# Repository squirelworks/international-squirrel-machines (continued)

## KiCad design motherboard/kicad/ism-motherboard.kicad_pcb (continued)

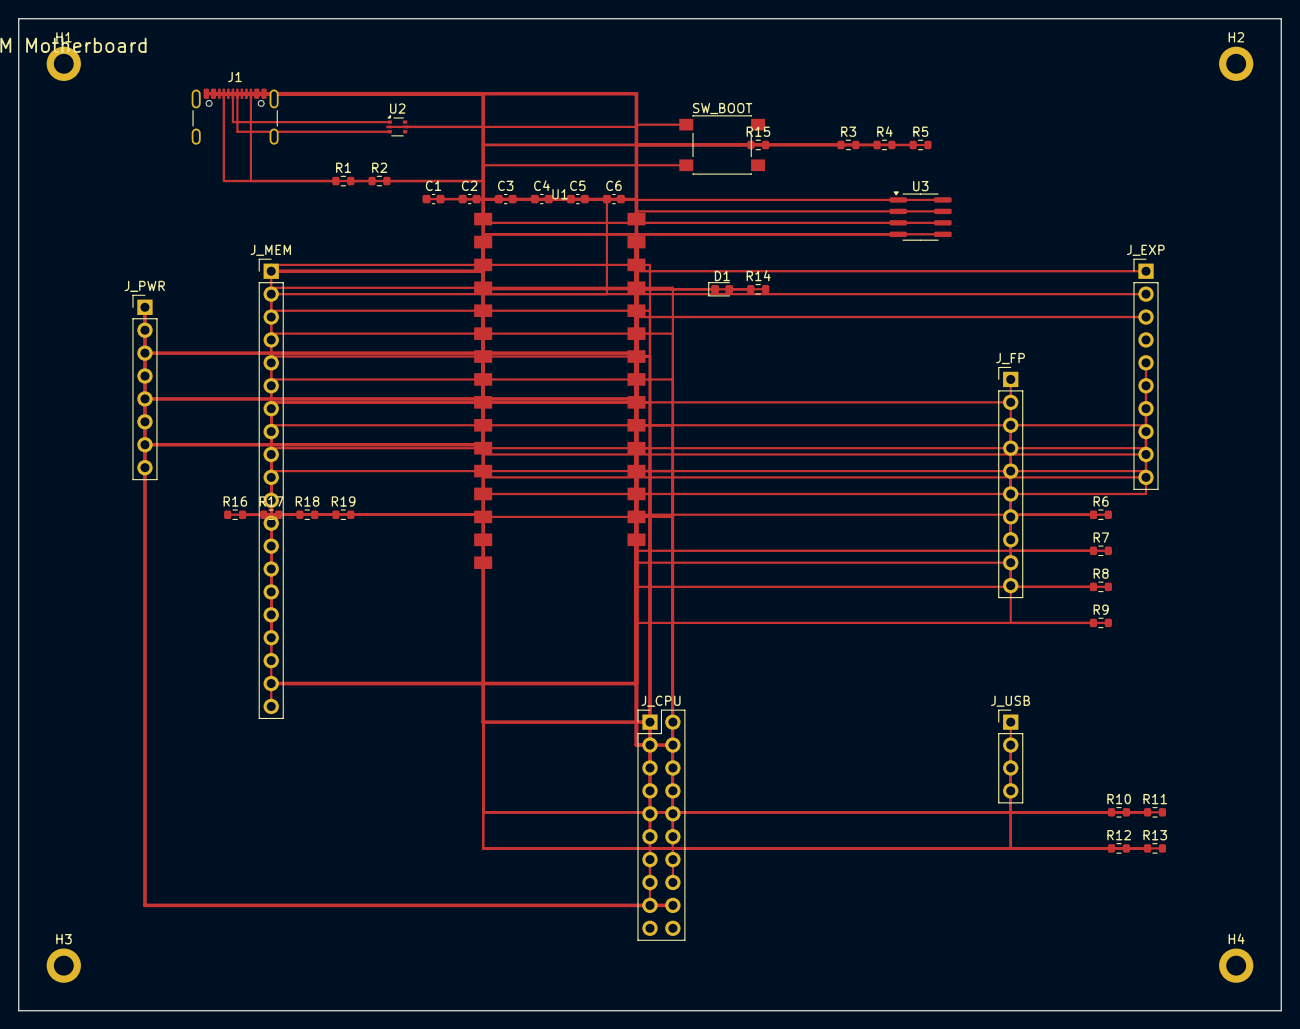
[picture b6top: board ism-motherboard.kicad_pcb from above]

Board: 4 copper layers, 140.0 x 110.0 mm, 41 parts (0 on the bottom side), 42 nets.

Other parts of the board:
H1, H2, H3, H4: M2; MountingHole_2.2mm_M2_DIN965_Pad

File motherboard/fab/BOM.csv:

Designator,Value,Footprint,Quantity,Manufacturer,MPN,LCSC,Notes
U1,RP2040_MOD,ISM_RP2040_Module,1,ISM,ISM-RP2040-MOD,,No LCSC — BMC / southbridge stand-in
U2,USBLC6-2SC6,SOT-666,1,ST,USBLC6-2SC6,C7519,ESD
U3,24LC02,SOIC-8,1,Microchip,24LC02B,C7500,Board ID
J1,USB4105,GCT USB-C 16P,1,GCT,USB4105-GF-A,C165948,BMC USB
J_PWR,ATX_PWR,PinHeader 1x08,1,,HDR-1x8,C124412,Bring-up power
J_MEM,MEM20,PinHeader 1x20,1,,HDR-1x20,C124419,Memory net map
J_CPU,CPU20,PinHeader 2x10,1,,HDR-2x10,C124384,CPU module
J_FP,ATX_FP,PinHeader 1x10,1,,HDR-1x10,C124413,Case FP
J_USB,MB_USB,PinHeader 1x04,1,,HDR-1x4,C124423,Case USB
J_EXP,EXP10,PinHeader 1x10,1,,HDR-1x10,C124413,Expansion
"R1,R2",5.1k,0603,2,,5.1k,C23244,CC
"R3,R4",4.7k,0603,2,,4.7k,C23141,I2C
"R5,R8,R9,R10-R13,R15-R19",10k,0603,13,,10k,C25804,
"R6,R7,R14",1k,0603,3,,1k,C21190,
C1-C6,100nF,0603,6,,100nF,C14663,
D1,LED,0603,1,,LED,C2286,
SW_BOOT,PTS645,PTS645,1,,PTS645,C318884,
H1-H4,M2,MountingHole,4,,,,No LCSC — mechanical NPTH

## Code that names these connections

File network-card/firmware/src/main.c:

/*
 * ISM Network Card firmware — SPI master bring-up for W5500 + EXP slave pins.
 * Module pad N → GP(N-2) for pads 2..13 (ISM convention).
 */
#include "pico/stdlib.h"
#include "hardware/gpio.h"
#include "hardware/spi.h"
#include "tusb.h"

#define PIN_EXP_SCK   0
#define PIN_EXP_MOSI  1
#define PIN_EXP_MISO  2
#define PIN_EXP_CS    3
#define PIN_ETH_SCLK  4  /* pad 6 */
#define PIN_ETH_MOSI  5  /* pad 7 */
#define PIN_ETH_MISO  6  /* pad 8 */
#define PIN_ETH_CS    7  /* pad 9 */
#define PIN_ETH_INT   10 /* pad 12 */
#define PIN_ETH_RST   11 /* pad 13 */
#define PIN_LED       17 /* pad 19 */

void tud_hid_report_complete_cb(uint8_t i, uint8_t const *r, uint16_t n) {
  (void)i; (void)r; (void)n;
}
uint16_t tud_hid_get_report_cb(uint8_t i, uint8_t id, hid_report_type_t t, uint8_t *b, uint16_t n) {
  (void)i; (void)id; (void)t; (void)b; (void)n; return 0;
}
void tud_hid_set_report_cb(uint8_t i, uint8_t id, hid_report_type_t t, uint8_t const *b, uint16_t n) {
  (void)i; (void)id; (void)t; (void)b; (void)n;
}

static void w5500_reset(void) {
  gpio_put(PIN_ETH_RST, 0);
  sleep_ms(2);
  gpio_put(PIN_ETH_RST, 1);
  sleep_ms(2);
}

int main(void) {
  gpio_init(PIN_LED); gpio_set_dir(PIN_LED, GPIO_OUT); gpio_put(PIN_LED, 0);

  gpio_init(PIN_EXP_CS); gpio_set_dir(PIN_EXP_CS, GPIO_IN); gpio_pull_up(PIN_EXP_CS);
  gpio_set_function(PIN_EXP_SCK, GPIO_FUNC_SPI);
  gpio_set_function(PIN_EXP_MOSI, GPIO_FUNC_SPI);
  gpio_set_function(PIN_EXP_MISO, GPIO_FUNC_SPI);

  spi_init(spi0, 8 * 1000 * 1000);
  gpio_set_function(PIN_ETH_SCLK, GPIO_FUNC_SPI);
  gpio_set_function(PIN_ETH_MOSI, GPIO_FUNC_SPI);
  gpio_set_function(PIN_ETH_MISO, GPIO_FUNC_SPI);
  gpio_init(PIN_ETH_CS); gpio_set_dir(PIN_ETH_CS, GPIO_OUT); gpio_put(PIN_ETH_CS, 1);
  gpio_init(PIN_ETH_RST); gpio_set_dir(PIN_ETH_RST, GPIO_OUT); gpio_put(PIN_ETH_RST, 1);
  gpio_init(PIN_ETH_INT); gpio_set_dir(PIN_ETH_INT, GPIO_IN); gpio_pull_up(PIN_ETH_INT);

  w5500_reset();
  tusb_init();

  absolute_time_t next = make_timeout_time_ms(400);
  bool on = false;
  while (true) {
    tud_task();
    if (absolute_time_diff_us(get_absolute_time(), next) <= 0) {
      on = !on;
      gpio_put(PIN_LED, on || !gpio_get(PIN_ETH_INT));
      next = make_timeout_time_ms(400);
    }
  }
}

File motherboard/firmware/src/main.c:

/*
 * ISM Motherboard BMC firmware — board-ID I2C + SPI expansion stub + activity LED.
 * Module pad N maps to GP(N-2) for pads 2..13 (ISM convention).
 */
#include "pico/stdlib.h"
#include "hardware/gpio.h"
#include "hardware/i2c.h"
#include "tusb.h"

#define PIN_CLK      0
#define PIN_CS       1
#define PIN_SDA      8   /* pad 10 */
#define PIN_SCL      9   /* pad 11 */
#define PIN_LED_ACT  18  /* pad 20 */
#define PIN_EXP_CS   23  /* pad 25 */
#define PIN_CPU_RST  17  /* pad 19 */

#define EEPROM_ADDR  0x50

void tud_hid_report_complete_cb(uint8_t i, uint8_t const *r, uint16_t n) {
  (void)i; (void)r; (void)n;
}
uint16_t tud_hid_get_report_cb(uint8_t i, uint8_t id, hid_report_type_t t, uint8_t *b, uint16_t n) {
  (void)i; (void)id; (void)t; (void)b; (void)n; return 0;
}
void tud_hid_set_report_cb(uint8_t i, uint8_t id, hid_report_type_t t, uint8_t const *b, uint16_t n) {
  (void)i; (void)id; (void)t; (void)b; (void)n;
}

int main(void) {
  gpio_init(PIN_LED_ACT); gpio_set_dir(PIN_LED_ACT, GPIO_OUT); gpio_put(PIN_LED_ACT, 0);
  gpio_init(PIN_CS); gpio_set_dir(PIN_CS, GPIO_OUT); gpio_put(PIN_CS, 1);
  gpio_init(PIN_EXP_CS); gpio_set_dir(PIN_EXP_CS, GPIO_OUT); gpio_put(PIN_EXP_CS, 1);
  gpio_init(PIN_CPU_RST); gpio_set_dir(PIN_CPU_RST, GPIO_OUT); gpio_put(PIN_CPU_RST, 1);

  i2c_init(i2c0, 100 * 1000);
  gpio_set_function(PIN_SDA, GPIO_FUNC_I2C);
  gpio_set_function(PIN_SCL, GPIO_FUNC_I2C);
  gpio_pull_up(PIN_SDA);
  gpio_pull_up(PIN_SCL);

  tusb_init();

  uint8_t addr = 0;
  uint8_t id = 0;
  i2c_write_blocking(i2c0, EEPROM_ADDR, &addr, 1, true);
  i2c_read_blocking(i2c0, EEPROM_ADDR, &id, 1, false);

  while (true) {
    tud_task();
    gpio_put(PIN_LED_ACT, 1);
    sleep_ms(40);
    gpio_put(PIN_LED_ACT, 0);
    sleep_ms(960);
    (void)id;
  }
}
